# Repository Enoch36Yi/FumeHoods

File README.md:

# SashSense

SashSense monitors fume hood sash position and whether someone is working at the hood. It is designed to beep when a user walks away and leaves the sash open. The wider project is working toward deployment across 191 UW fume hoods, supported by a UW STF Green Building Award.

I selected sensors, tested breadboard circuits, designed PCBs and built earlier ESP32 prototypes, coordinating team member contributions.

The in-hood node measures sash opening and temperature/humidity. The presence node uses VL53L1X and an AMG8833 thermopile array; it builds on SEAL's Firefly human-presence project.

## Schematics and PCB previews

| Board | Schematic | 3D PCB |
| --- | --- | --- |
| Node 1 | [JPG](previews/SashSense_node1_schematic.jpg) | [JPG](previews/SashSense_node1_pcb_3d.jpg) |
| Node 2 | [JPG](previews/SashSense_node2_schematic.jpg) | [JPG](previews/SashSense_node2_pcb_3d.jpg) |

The PCB previews are CAD renders; some component models are missing.

## Node 1 — in-hood board

Open `SashSense_node1.kicad_pro` in KiCad 10. The matching schematic and board use the same filename stem.

*CAD render, not a hardware photograph.*

[Node 1 schematic](SashSense_node1.pdf)

This earlier revision contains ESP32-WROOM-32E, SHT31, USB-C, CP2102N and AMS1117-3.3. Its distance sensor is a VL53L1X.

## Node 2 — presence-board reconstruction

Open [SashSense_node2/Firefly_pcb2.kicad_pro](SashSense_node2/Firefly_pcb2.kicad_pro). The circuit uses ESP32-S3-WROOM-1-N8, VL53L1X, AMG8833 and a transistor-driven piezo beeper. Project-local symbols, footprints, layout builders and verification scripts are included.

*CAD render of the complete 160 × 60 mm board, not a hardware photograph. Some part models are absent.*

The outline was first drawn as a provisional 500 × 500 mm board and has since been trimmed to the populated area; placement and routing did not change. Sensor positions and the four corner mounting holes are provisional. Placement and routing decisions are documented in the layout review below.

[Node 2 schematic](SashSense_node2/outputs/Firefly_pcb2_schematic.pdf) · [Layout review](SashSense_node2/docs/pcb_layout_review.md) · [Open, check and regenerate](SashSense_node2/README.md)

## Current checks and unfinished work

Saved KiCad 10.0.5 check results:

| Check | Node 1 | Firefly node 2 |
| --- | --- | --- |
| ERC errors/warnings | 0 / 0 | 0 / 0 |
| Configured DRC findings | 1 | 0 |
| Unconnected items | 0 | 0 |
| Configured schematic/PCB parity issues | 0 | 0 |

A stricter check reports 24 footprint-filter metadata mismatches. The generator needs that fix before schematic regeneration. Script-check results and the stricter-check details are in the [layout review](SashSense_node2/docs/pcb_layout_review.md).

Neither revision is released for fabrication. Node 1's one DRC finding is its ESP32 footprint differing from KiCad's library copy (0.3 mm instead of 0.2 mm thermal vias), kept on purpose. Firefly's beeper is externally mounted, and needs mounting and optical openings, a regulated 3.3 V harness, and a fabricator DFM review. 

The root reports describe Node 1; Firefly reports are under `SashSense_node2/reports/`.

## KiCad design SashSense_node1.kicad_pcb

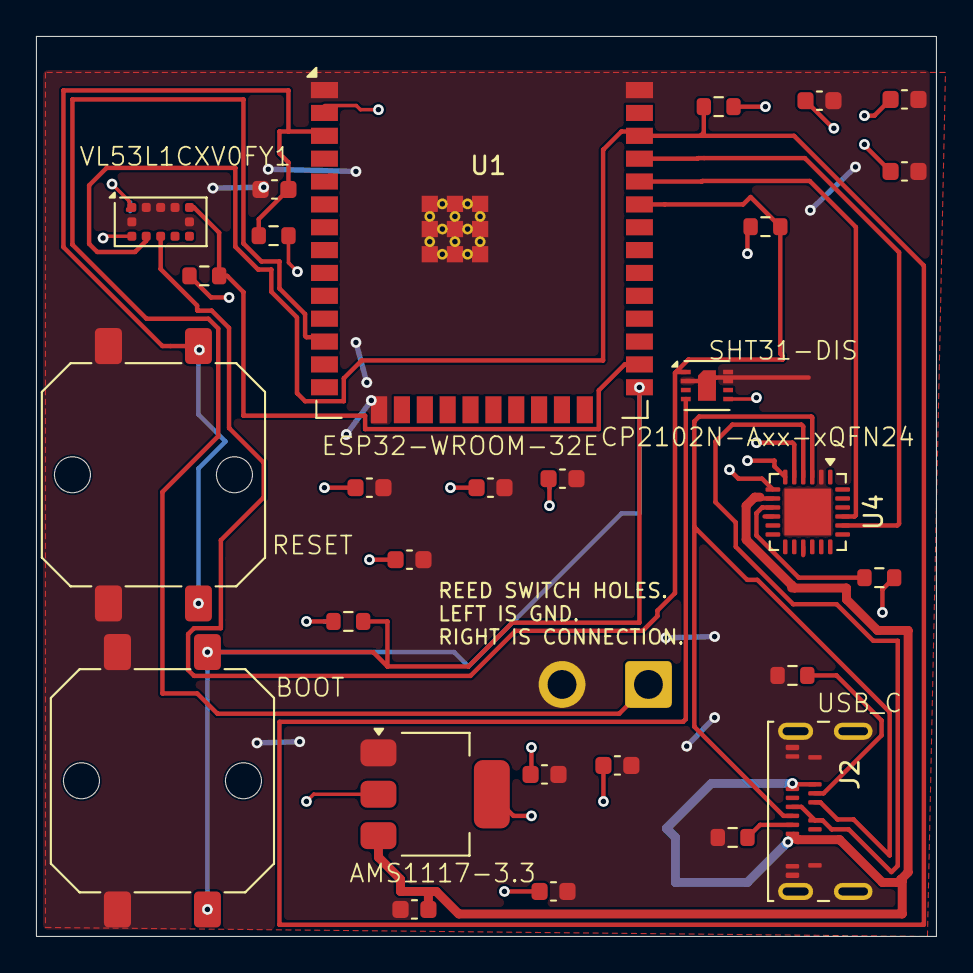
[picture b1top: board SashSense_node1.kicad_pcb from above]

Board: 2 copper layers, 50.0 x 50.0 mm, 29 parts (0 on the bottom side), 16 nets.

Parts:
C1, C2, C3, C4, C11, C12: 100nF; C_0603_1608Metric
C5, C6, C7: 10uF; C_0603_1608Metric
C8, C9: 4.7 uF; C_0603_1608Metric
C10: 1uF; C_0603_1608Metric
J1: Conn_01x02_Pin; SolderWire-0.75sqmm_1x02_P4.8mm_D1.25mm_OD2.3mm
J2: USB_C_Receptacle_USB2.0_16P; USB_C_Receptacle_Amphenol_124019772112A
R1, R2, R3, R4: 10k; R_0603_1608Metric
R5, R6: 4.7k; R_0603_1608Metric
R7, R8: 5.1k; R_0603_1608Metric
SW1: reset; SW_Push_1P1T_NO_CK_PTS125Sx43PSMTR
SW2: boot; SW_Push_1P1T_NO_CK_PTS125Sx43PSMTR
U1: ESP32-WROOM-32E
U2: SHT31-DIS; Sensirion_DFN-8-1EP_2.5x2.5mm_P0.5mm_EP1.1x1.7mm
U3: AMS1117-3.3; SOT-223-3_TabPin2
U4: CP2102N-Axx-xQFN24; QFN-24-1EP_4x4mm_P0.5mm_EP2.6x2.6mm
U5: VL53L1CXV0FY1; ST_VL53L1x

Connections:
+3.3V: C1.1, C2.1, C3.1, C4.1, C6.1, C7.1, C8.1, C9.1, C11.1, C12.1, R1.1, R2.1, R3.1, R4.1, R5.1, R6.1, U1.2 (VDD), U2.5 (VDD), U3.2 (VO), U4.5 (VIO), U4.6 (VDD), U4.7 (VREGIN), U5.1 (AVDDVCSEL), U5.11 (AVDD)
+5V: C5.1, J2.A4 (VBUS), J2.A9 (VBUS), J2.B4 (VBUS), J2.B9 (VBUS), U3.3 (VI), U4.8 (VBUS)
/BOOT: R2.2, SW2.1, U1.25 (IO0)
/CP_RST: R4.2, U4.9 (~RST)
/SCL: R6.2, U1.36 (IO22), U2.4 (SCL), U5.10 (SCL)
/SDA: R5.2, U1.33 (IO21), U2.1 (SDA), U5.9 (SDA)
/UORXD: U1.34 (RXD0/IO3), U4.21 (TXD)
/UOTXD: U1.35 (TXD0/IO1), U4.20 (RXD)
/USB_DM: J2.A7 (D-), J2.B7 (D-), U4.4 (D-)
/USB_DP: J2.A6 (D+), J2.B6 (D+), U4.3 (D+)
/XSHUT: R3.2, U1.26 (IO4), U5.5 (XSHUT)
GND: C1.2, C2.2, C3.2, C4.2, C5.2, C6.2, C7.2, C8.2, C9.2, C10.2, C11.2, C12.2, J1.2, J2.A1 (GND), J2.A12 (GND), J2.B1 (GND), J2.B12 (GND), J2.SH (SHIELD), R7.2, R8.2, SW1.2, SW2.2, U1.1 (GND), U1.15 (GND), U1.38 (GND), U1.39 (GND), U2.2 (ADDR), U2.7 (R), U2.8 (VSS), U2.9 (VSS), U3.1 (GND), U4.2 (GND), U4.25 (GND), U5.2 (AVSSVCSEL), U5.3 (GND), U5.4 (GND), U5.6 (GND), U5.12 (GND)
unnamed: J1.1, U1.12 (IO27)
unnamed: J2.A5 (CC1), R7.1
unnamed: J2.B5 (CC2), R8.1
unnamed: C10.1, R1.2, SW1.1, U1.3 (EN)

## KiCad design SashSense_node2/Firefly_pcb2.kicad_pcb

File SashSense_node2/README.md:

# Firefly presence board

A new reconstruction of the SashSense presence node: ESP32-S3-WROOM-1-N8, bare VL53L1X, bare AMG8833 and a transistor-driven piezo beeper. The two-layer board is 160 × 60 mm, trimmed to the populated area from an earlier provisional 500 × 500 mm outline. It is routed and digitally checked, but has not been fabricated or tested as hardware.

## Open it

Use KiCad 10.0.5 and open `Firefly_pcb2.kicad_pro`. Symbols and footprints are under `libraries/`, with project-relative library tables. Standard KiCad 3D model libraries are used where available; some components have no 3D body in the render.

The board takes externally regulated 3.3 V at J1. J2 is a set of provisional 3.3 V UART/service pads, not an established mating connector. USB D+/D− are unused. Existing-system host and firmware/backend compatibility still need to be established.

## Reproduce the checks

Run from this directory. KiCad's Python interpreter provides `pcbnew`; ordinary Python does not include it.

```powershell
$kc = 'C:\Program Files\KiCad\10.0\bin\kicad-cli.exe'
$kp = 'C:\Program Files\KiCad\10.0\bin\python.exe'
& $kc sch export netlist --format kicadxml --output reports/netlist.xml Firefly_pcb2.kicad_sch
& $kc sch erc --severity-all --format json --output reports/erc.json Firefly_pcb2.kicad_sch
& $kp scripts/verify_schematic.py
& $kc pcb drc --schematic-parity --refill-zones --severity-all --format json --output reports/drc.json Firefly_pcb2.kicad_pcb
& $kp scripts/verify_pcb.py
```

`make_pcb_outputs.ps1` runs the larger pipeline, including renders, Gerbers, drill files, BOM/CPL and the output checks. The manufacturing review files are generated on demand under `outputs/manufacturing_P2_PROVISIONAL`; they are not committed here. The saved output report covers the complete local package.

```powershell
.\scripts\make_pcb_outputs.ps1
```

To regenerate the routed board, export the netlist first, then use `& $kp scripts/layout_pcb.py --overwrite`. That replaces manual layout edits; the outline comes from `OUTLINE_MM` in `scripts/cad_common.py`. The older schematic generator, `build_project.py`, has a known footprint-filter metadata bug, and its legacy `--build-pcb` branch still contains the original 500 × 500 mm draft geometry (it now exits before writing a board). Do not run it just to open or check this revision.

## Results and release blockers

The saved KiCad checks report no ERC errors or warnings, configured DRC violations, unconnected items or configured parity issues. A stricter run reports 24 footprint-filter metadata mismatches. Detailed results, including the script checks, are in the [layout review](docs/pcb_layout_review.md) and `reports/drc_strict.json`.

Beeper sourcing, support pattern, sensor openings, board thickness, power harness and a fabricator DFM review remain open. J1 currently has no reverse-polarity, TVS or fuse protection. RF performance, optical behavior, self-heating, physical fit and assembled operation still require hardware tests.

See the [layout review](docs/pcb_layout_review.md) for placement and routing decisions and the [bring-up checklist](docs/bringup_checklist.md) for the first assembled board. The electrical review links to manufacturer datasheets.

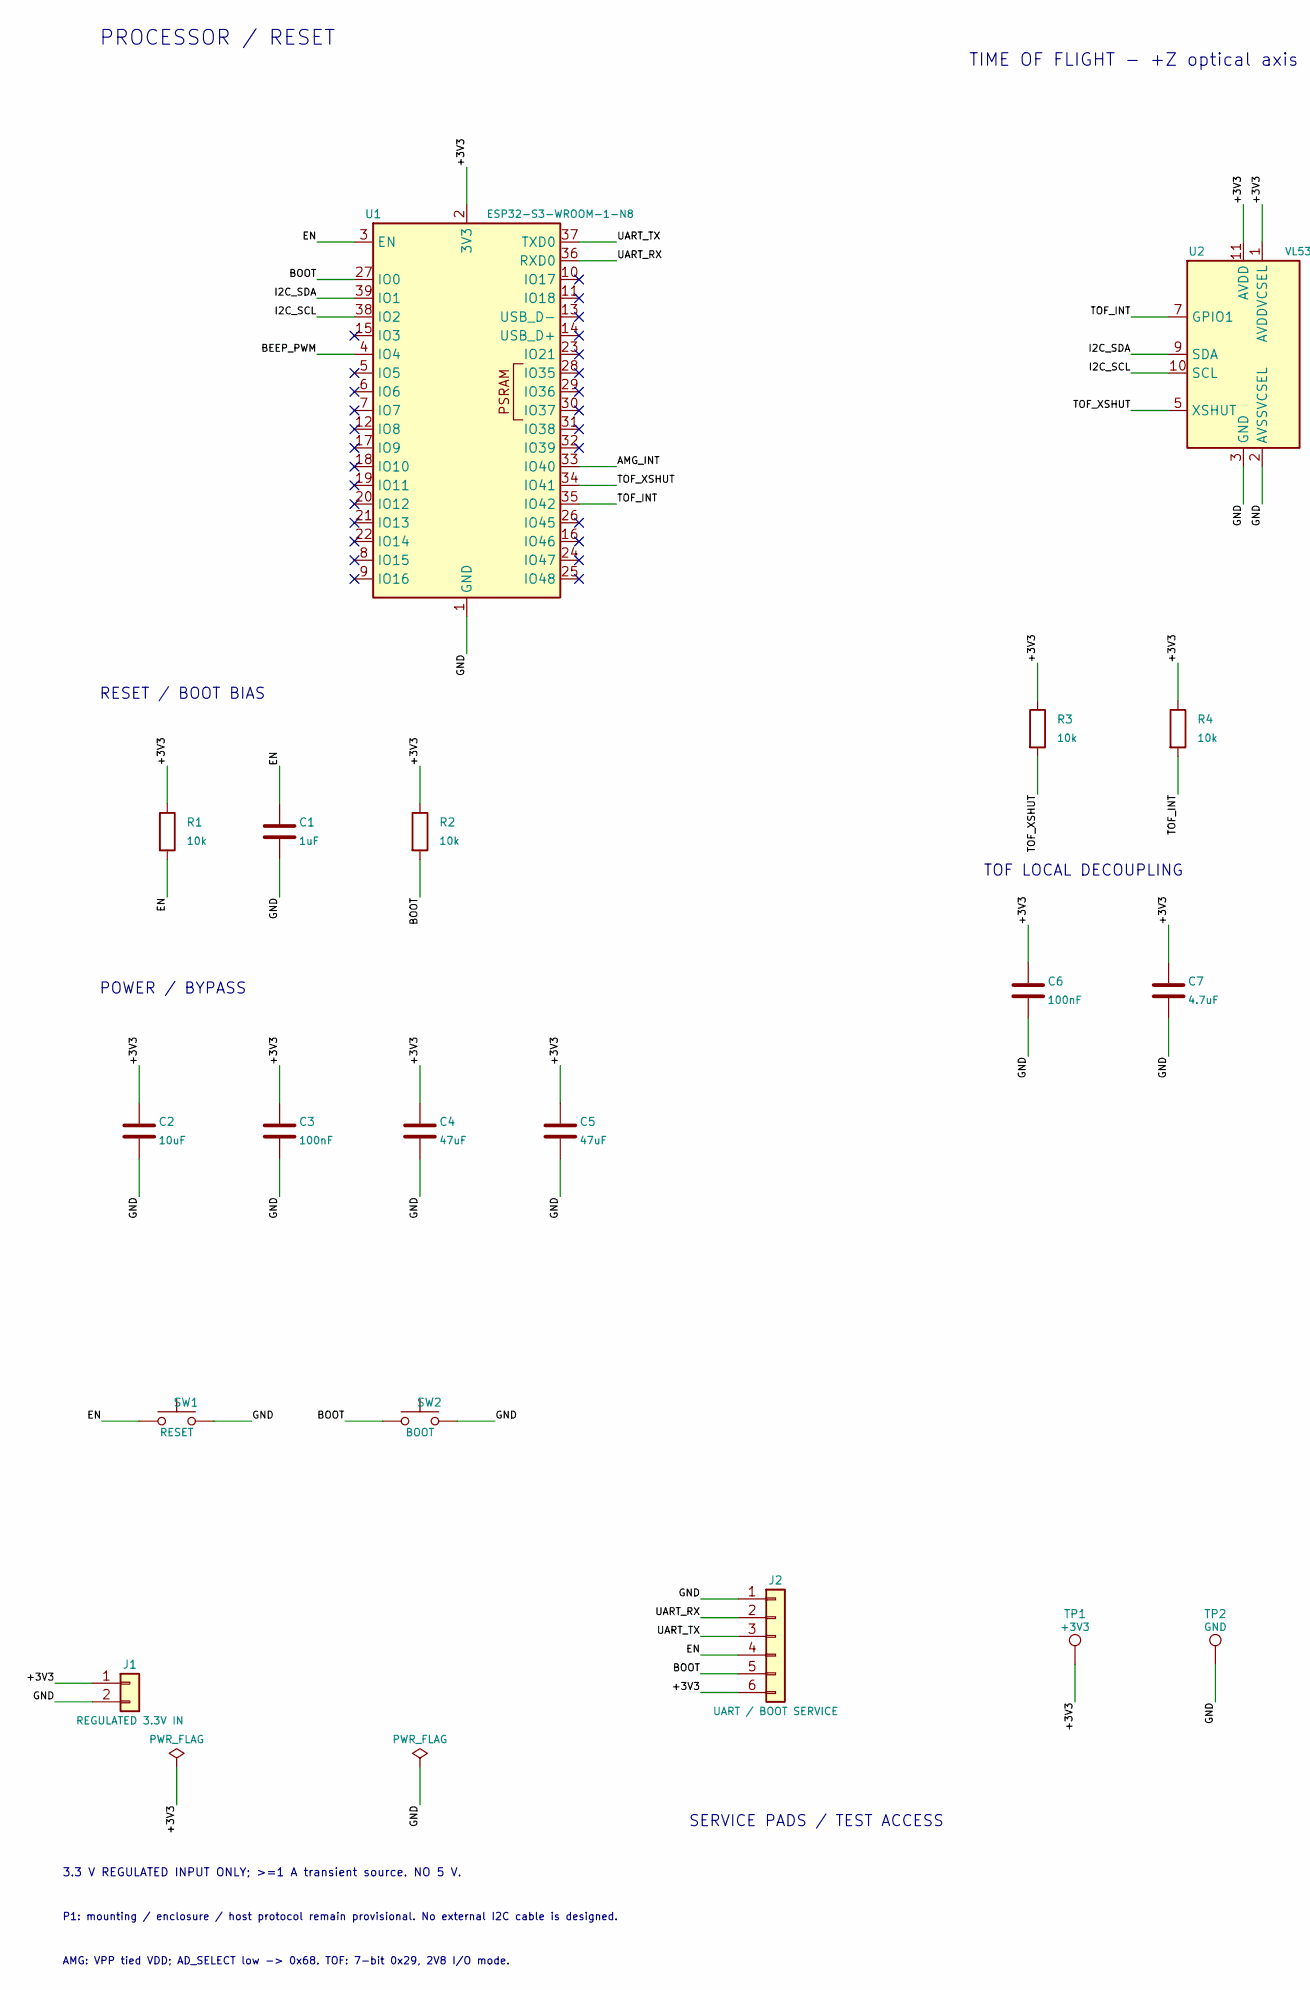
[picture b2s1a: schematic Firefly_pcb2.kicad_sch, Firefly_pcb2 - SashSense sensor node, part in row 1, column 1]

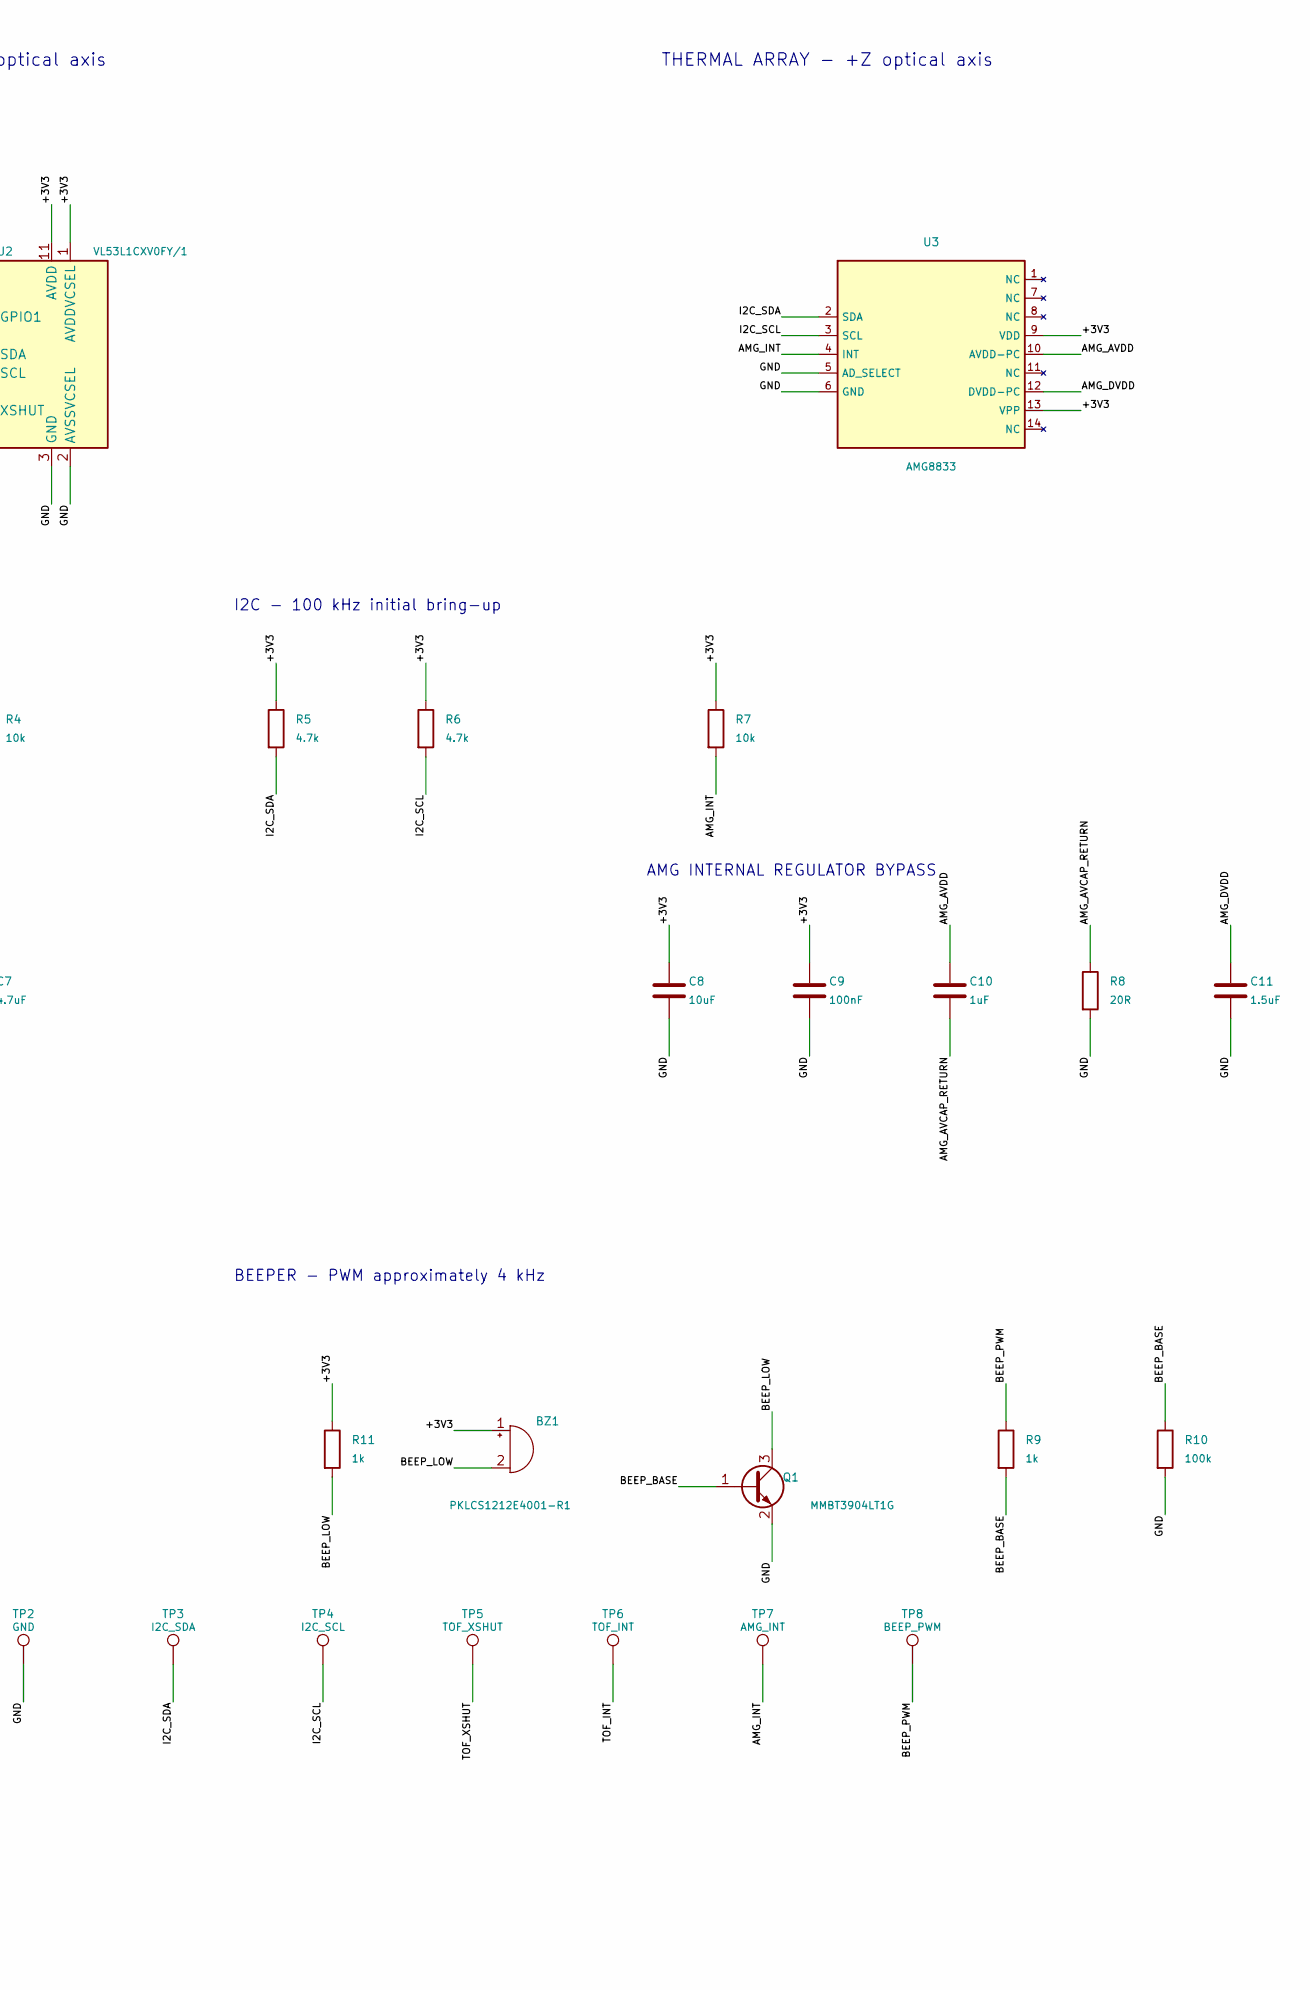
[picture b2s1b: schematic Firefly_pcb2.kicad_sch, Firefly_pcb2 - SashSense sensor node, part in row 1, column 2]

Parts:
BZ1: PKLCS1212E4001-R1; Buzzer_Murata_PKLCS1212E; MPN PKLCS1212E4001-R1
C1, C10: 1uF; C_0603_1608Metric; MPN GRM188R61A105KA61D
C2, C8: 10uF; C_0805_2012Metric; MPN GRM21BR61A106KE19L
C3, C6, C9: 100nF; C_0603_1608Metric; MPN GRM188R71C104KA01D
C4, C5: 47uF; C_1206_3216Metric; MPN GRM31CR60J476ME19L
C7: 4.7uF; C_0603_1608Metric; MPN GRM188R60J475KE19D
C11: 1.5uF; C_0603_1608Metric; MPN GRM188R61A155KA61D
J1: REGULATED 3.3V IN; SolderWire-0.75sqmm_1x02_P4.8mm_D1.25mm_OD2.3mm; MPN PCB FEATURE
J2: UART / BOOT SERVICE; ServicePads_1x06; MPN PCB FEATURE
Q1: MMBT3904LT1G; SOT-23; MPN MMBT3904LT1G
R1, R2, R3, R4, R7: 10k; R_0603_1608Metric; MPN RC0603FR-0710KL
R5, R6: 4.7k; R_0603_1608Metric; MPN RC0603FR-074K7L
R8: 20R; R_0603_1608Metric; MPN RC0603FR-0720RL
R9, R11: 1k; R_0603_1608Metric; MPN RC0603FR-071KL
R10: 100k; R_0603_1608Metric; MPN RC0603FR-07100KL
SW1: RESET; SW_SPST_TL3342; MPN TL3342F160QG
SW2: BOOT; SW_SPST_TL3342; MPN TL3342F160QG
TP1: +3V3; TestPoint_Pad_D1.5mm; MPN PCB FEATURE
TP2: GND; TestPoint_Pad_D1.5mm; MPN PCB FEATURE
TP3: I2C_SDA; TestPoint_Pad_D1.5mm; MPN PCB FEATURE
TP4: I2C_SCL; TestPoint_Pad_D1.5mm; MPN PCB FEATURE
TP5: TOF_XSHUT; TestPoint_Pad_D1.5mm; MPN PCB FEATURE
TP6: TOF_INT; TestPoint_Pad_D1.5mm; MPN PCB FEATURE
TP7: AMG_INT; TestPoint_Pad_D1.5mm; MPN PCB FEATURE
TP8: BEEP_PWM; TestPoint_Pad_D1.5mm; MPN PCB FEATURE
U1: ESP32-S3-WROOM-1-N8; ESP32-S3-WROOM-1; MPN ESP32-S3-WROOM-1-N8
U2: VL53L1CXV0FY/1; ST_VL53L1x; MPN VL53L1CXV0FY/1
U3: AMG8833; MPN AMG8833

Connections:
/+3V3: BZ1.1 (+), C2.1, C3.1, C4.1, C5.1, C6.1, C7.1, C8.1, C9.1, J1.1, J2.6, R1.1, R2.1, R3.1, R4.1, R5.1, R6.1, R7.1, R11.1, TP1.1, U1.2 (3V3), U2.1 (AVDDVCSEL), U2.11 (AVDD), U3.9 (VDD), U3.13 (VPP)
/AMG_AVCAP_RETURN: C10.2, R8.1
/AMG_AVDD: C10.1, U3.10 (AVDD-PC)
/AMG_DVDD: C11.1, U3.12 (DVDD-PC)
/AMG_INT: R7.2, TP7.1, U1.33 (IO40), U3.4 (INT)
/BEEP_BASE: Q1.1 (B), R9.2, R10.1
/BEEP_LOW: BZ1.2 (-), Q1.3 (C), R11.2
/BEEP_PWM: R9.1, TP8.1, U1.4 (IO4)
/BOOT: J2.5, R2.2, SW2.1, U1.27 (IO0)
/EN: C1.1, J2.4, R1.2, SW1.1, U1.3 (EN)
/GND: C1.2, C2.2, C3.2, C4.2, C5.2, C6.2, C7.2, C8.2, C9.2, C11.2, J1.2, J2.1, Q1.2 (E), R8.2, R10.2, SW1.2, SW2.2, TP2.1, U1.1 (GND), U1.40 (GND), U1.41 (GND), U2.2 (AVSSVCSEL), U2.3 (GND), U2.4 (GND), U2.6 (GND), U2.12 (GND), U3.5 (AD_SELECT), U3.6 (GND)
/I2C_SCL: R6.2, TP4.1, U1.38 (IO2), U2.10 (SCL), U3.3 (SCL)
/I2C_SDA: R5.2, TP3.1, U1.39 (IO1), U2.9 (SDA), U3.2 (SDA)
/TOF_INT: R4.2, TP6.1, U1.35 (IO42), U2.7 (GPIO1)
/TOF_XSHUT: R3.2, TP5.1, U1.34 (IO41), U2.5 (XSHUT)
/UART_RX: J2.2, U1.36 (RXD0)
/UART_TX: J2.3, U1.37 (TXD0)

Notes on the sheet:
PROCESSOR / RESET
TIME OF FLIGHT - +Z optical axis
THERMAL ARRAY - +Z optical axis
RESET / BOOT BIAS
I2C - 100 kHz initial bring-up
POWER / BYPASS
TOF LOCAL DECOUPLING
AMG INTERNAL REGULATOR BYPASS
BEEPER - PWM approximately 4 kHz
SERVICE PADS / TEST ACCESS
3.3 V REGULATED INPUT ONLY; >=1 A transient source. NO 5 V.
P1: mounting / enclosure / host protocol remain provisional. No external I2C cable is designed.
AMG: VPP tied VDD; AD_SELECT low -> 0x68. TOF: 7-bit 0x29, 2V8 I/O mode.

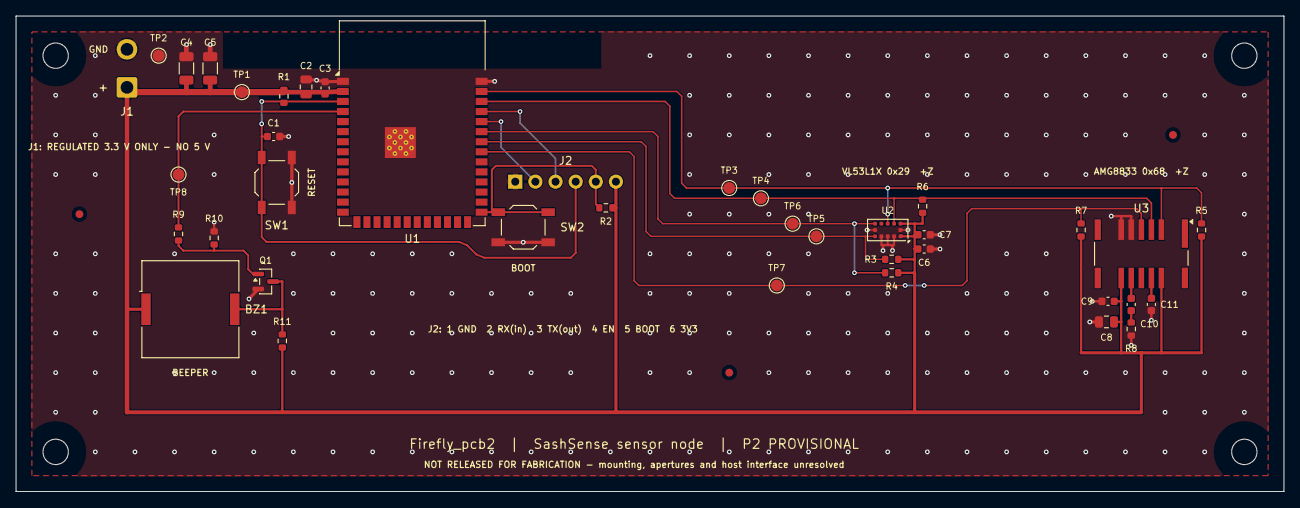
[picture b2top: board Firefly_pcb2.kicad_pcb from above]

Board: 2 copper layers, 160.0 x 60.0 mm, 46 parts (0 on the bottom side), 17 nets.

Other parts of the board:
FID1, FID2, FID3: Fiducial; Fiducial_1mm_Mask2mm
H1, H2, H3, H4: M3 SUPPORT - PROVISIONAL; MountingHole_3.2mm_M3
